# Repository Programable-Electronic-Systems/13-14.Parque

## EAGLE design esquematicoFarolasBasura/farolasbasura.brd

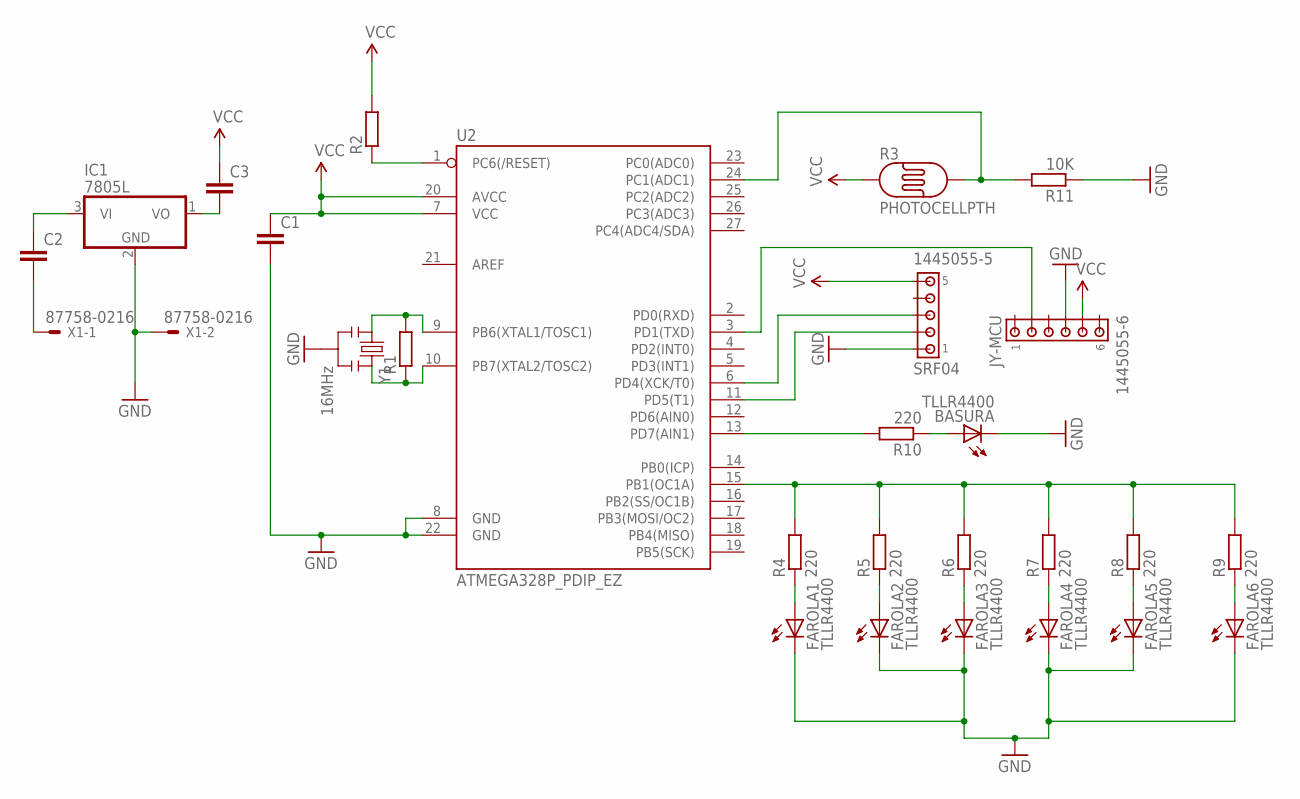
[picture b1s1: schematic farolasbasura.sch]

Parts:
BASURA: TLLR4400; LED3MM
C1, C2, C3: C-EU050-025X075; C050-025X075
FAROLA1, FAROLA2, FAROLA3, FAROLA4, FAROLA5, FAROLA6: TLLR4400; LED3MM
IC1: 7805L; TO92
JY-MCU: 1445055-6
R1, R2: R-EU_0204/7; 0204/7
R3: PHOTOCELLPTH; PHOTOCELL
R4, R5, R6, R7, R8, R9, R10: 220; 0204/7
R11: 10K; 0204/7
SRF04: 1445055-5
U2: ATMEGA328P_PDIP_EZ; DIL28-EZ
X1: 87758-0216
Y1: 16MHz; RESONATOR-SMD

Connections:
GND: BASURA.K (C), C1.2, FAROLA1.K (C), FAROLA2.K (C), FAROLA3.K (C), FAROLA4.K (C), FAROLA5.K (C), FAROLA6.K (C), IC1.2 (GND), JY-MCU.4, R11.1, SRF04.1, U2.8 (GND), U2.22 (GND), X1.2, Y1.2
unnamed: R1.2, U2.9 (PB6(XTAL1/TOSC1)), Y1.1
unnamed: R1.1, U2.10 (PB7(XTAL2/TOSC2)), Y1.3
unnamed: R2.1, U2.1 (PC6(/RESET))
unnamed: FAROLA1.A, R4.1
unnamed: FAROLA2.A, R5.1
unnamed: C2.1, IC1.3 (VI)
unnamed: FAROLA3.A, R6.1
unnamed: FAROLA4.A, R7.1
unnamed: FAROLA5.A, R8.1
unnamed: FAROLA6.A, R9.1
unnamed: BASURA.A, R10.1
unnamed: R10.2, U2.13 (PD7(AIN1))
unnamed: R3.2, R11.2, U2.24 (PC1(ADC1))
unnamed: C2.2, X1.1
unnamed: C3.2, IC1.1 (VO)
unnamed: SRF04.2, U2.11 (PD5(T1))
unnamed: R4.2, R5.2, R6.2, R7.2, R8.2, R9.2, U2.15 (PB1(OC1A))
unnamed: SRF04.3, U2.6 (PD4(XCK/T0))
unnamed: JY-MCU.2, U2.3 (PD1(TXD))
VCC: C1.1, C3.1, JY-MCU.5, R2.2, R3.1, SRF04.5, U2.7 (VCC), U2.20 (AVCC)

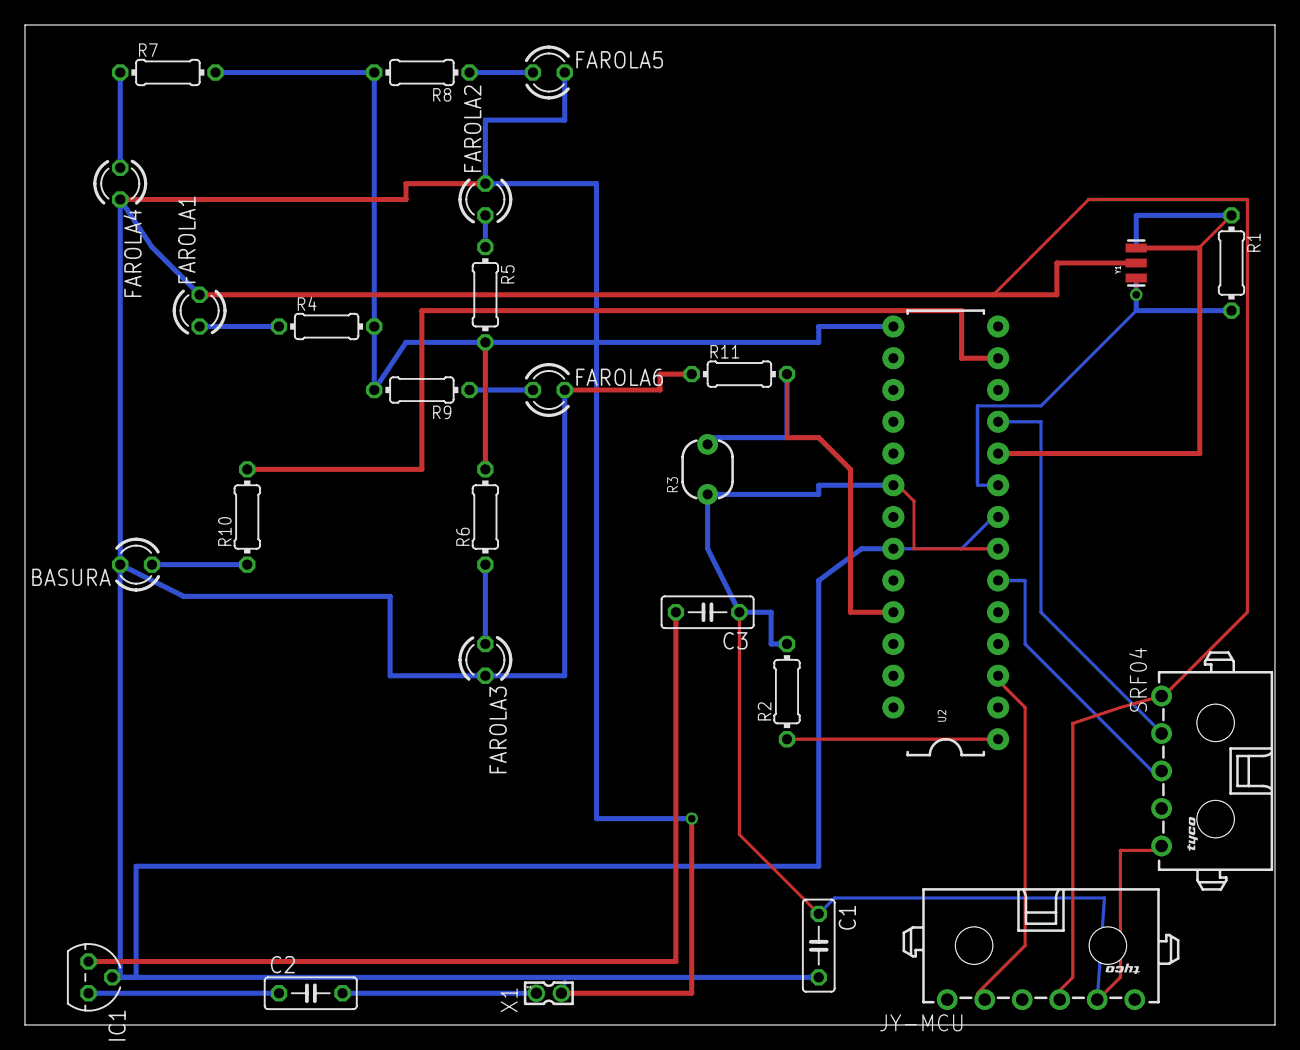
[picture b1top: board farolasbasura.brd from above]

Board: 2 copper layers, 100.0 x 80.0 mm, 27 parts (0 on the bottom side), 21 nets.

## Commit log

2013-11-27 +papeleraFarolas
2013-11-28 Anyadida pantalla LCD
2013-12-11 Anyadido esquematico del arduino Farolas
2014-01-14 +README

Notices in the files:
parts and their libraries:
SparkFun-DigitalIC: Licensing: CC v3.0 Share-Alike You are welcome to use this library for commercial purposes.
